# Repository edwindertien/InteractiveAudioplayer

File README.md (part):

# Interactive Audio Player
### Seven wearable players · Teensy 4.1 · 7.1 multichannel audio · NFC hand units · haptics

An embedded system for immersive, location-and-encounter based experiences. Each of up to
seven wearers carries a **hand unit** (NFC reader, distance sensor, vibration motor, LED strip).
Touching a hand unit to an **NFC tag** — another person's tag, a narrator tag, an overlay tag
or the start tag — changes what that wearer hears: the audio, a narration layer, overlays,
sound effects and a haptic channel that is felt through the body. The audio itself is a single
8-channel WAV file on an SD card inside each player.

This README is in two parts.

* **Part I — Operation manual:** preparing audio, the SD card and the configuration files,
  pairing the units, and running a show. Everything here needs no programming.
* **Part II — Building and programming:** hardware, setting up VS Code and PlatformIO, flashing
  the three devices, the project structure, and how the software works.

Background on design decisions, dead ends and open issues lives in [Context.md](Context.md).

> **Figures.** Every figure is a PNG; click it for the zoomable SVG. They are generated by
> `tools/make_docs.py` (see [section 17](#17-regenerating-the-figures)).

## Contents

**Part I — Operation manual**
1. [The system at a glance](#1-the-system-at-a-glance)
2. [The workflow in one picture](#2-the-workflow-in-one-picture)
3. [Preparing the audio](#3-preparing-the-audio)
4. [Preparing the SD card](#4-preparing-the-sd-card)
5. [Tags and the configuration files](#5-tags-and-the-configuration-files)
6. [Pairing hand units and body bridges](#6-pairing-hand-units-and-body-bridges)
7. [Running a show](#7-running-a-show)
8. [Changing files without removing the card (USB mode)](#8-changing-files-without-removing-the-card-usb-mode)
9. [Command reference](#9-command-reference)
10. [Troubleshooting](#10-troubleshooting)

**Part II — Building and programming**

11. [Hardware](#11-hardware)
12. [Setting up the development environment](#12-setting-up-the-development-environment)
13. [Building and flashing](#13-building-and-flashing)
14. [Project structure](#14-project-structure)
15. [How it works](#15-how-it-works)
16. [Tools reference](#16-tools-reference)
17. [Regenerating the figures](#17-regenerating-the-figures)

---

# Part I — Operation manual

## 1. The system at a glance

Each player is a set of three devices plus the wearer's tags:

| Device | What it is | What it does |
|---|---|---|
| **Hand unit** | ESP32-S3 SuperMini + PN532 NFC + VL53L0X distance sensor + vibration motor + 5-LED strip + LiPo | Reads tags, feels the distance to a hand, gives instant feedback (vibration, light) and reports to the body bridge |
| **Body bridge** | ESP32-S3 SuperMini | Receives the hand unit's wireless data (ESP-NOW) and passes it to the Teensy over a two-wire serial link; sends a heartbeat back |
| **Player** | Teensy 4.1 + SD card + PCM5102A (headphones) + MAX98357A (haptics) + LED ring | Plays the experience, decides what a tag means, drives headphones and the haptic transducer |

*Seven players run side by side, each with its own hand unit, body bridge, Teensy and SD card.
The pairs are independent: a hand unit talks to exactly one body bridge.*

## 2. The workflow in one picture

Everything the experience designer edits is a **file**. Nothing in this manual needs a firmware
change. The short version:

1. Export five stems from Ableton and run `assemble_71.sh` → `experience.wav`.  → [section 3](#3-preparing-the-audio)
2. Format the SD cards and copy the files; clean the hidden macOS files.  → [section 4](#4-preparing-the-sd-card)
3. Read the tag UIDs, fill in `tag_catalogue.json`, run `generate_player_configs.py` → seven `config.json`.  → [section 5](#5-tags-and-the-configuration-files)
4. Pair each hand unit with its body bridge.  → [section 6](#6-pairing-hand-units-and-body-bridges)
5. Power everything up and run the show.  → [section 7](#7-running-a-show)

**Tools you need on the Mac/PC:** Python 3, `ffmpeg` (`brew install ffmpeg`), and a serial
monitor (VS Code with PlatformIO, see [section 12](#12-setting-up-the-development-environment),
or any terminal program at 115200 baud).

---

## 3. Preparing the audio

### 3.1 Export the stems from Ableton

Export five files — all **the same length**, on the same tempo grid, **44100 Hz, 16-bit**:

| File | Channels | Content |
|---|---|---|
| `base.wav` | stereo | The main music bed |
| `narr.wav` | **mono** | Narration / operator cues |
| `ov1.wav` | stereo | Overlay stem 1 |
| `ov2.wav` | stereo | Overlay stem 2 |
| `haptic.wav` | **mono** | Low-frequency content that is felt, not heard (the LFE channel) |

*The Ableton arrangement: base, narration, two overlays and the haptic stem exported separately.*

> **Mono export in Ableton:** *File → Export Audio/Video* → tick **Convert to Mono**.

### 3.2 Assemble the 8-channel file

```bash
chmod +x experience/assemble_71.sh
./experience/assemble_71.sh base.wav narr.wav ov1.wav ov2.wav haptic.wav experience.wav
```

The script checks every stem's channel count before merging, so a wrong export can no longer
silently shift every later channel:

* `narr.wav` / `haptic.wav` exported as **stereo** → reduced to mono (`(L+R)/2`; set
  `MONO_MODE=left` to take the left channel only). A dual-mono file keeps its exact level.
* `base.wav` / `ov1.wav` / `ov2.wav` exported as **mono** → duplicated to both channels.
* Anything with more than 2 channels, or a file that is not audio → refused with a message.
* The finished file must be **8 channels at 44100 Hz**; if not, it is deleted and the script
  fails. An existing `experience.wav` is left alone if the script fails before writing.
* **Different stem lengths:** the output is cut to the *shortest* stem. The script prints a
  warning with the shortest and longest length — fix the export, otherwise the end of the
  longer stems is silently lost.

Channel order of `experience.wav` (standard 7.1):

| Index | Name | Content | Goes to |
|---|---|---|---|
| 0 | FL | base L | headphones L (always on) |
| 1 | FR | base R | headphones R (always on) |
| 2 | FC | narration | both ears, fades in/out when toggled |
| 3 | LFE | haptic | MAX98357A → haptic transducer, and the player's LED ring |
| 4 | BL | overlay 1 L | headphones L, fades in/out when toggled |
| 5 | BR | overlay 1 R | headphones R, fades in/out when toggled |
| 6 | SL | overlay 2 L | headphones L, fades in/out when toggled |
| 7 | SR | overlay 2 R | headphones R, fades in/out when toggled |

A 7.5-minute experience is about **317 MB** (450 s × 44 100 × 2 bytes × 8 channels).

### 3.3 The sound effects

Three short effects give feedback for tag events. They are loaded into RAM at boot and played
without touching the SD card.

| File | Played when | Slot |
|---|---|---|
| `fx_connect.wav` | a person tag was accepted (a new chapter starts) | 4 |
| `fx_denied.wav` | a person tag was refused (lock on and not in base, or the show is ending) | 5 |
| `fx_ready.wav` | an encounter has ended and you are back in base, ready for the next | 6 |

**Format requirement: 16-bit PCM, mono, 44.1 kHz, up to about 2 seconds.** The player labels
every effect as mono 44.1 kHz and does not resample, so a stereo or 48 kHz file plays at the
wrong speed. The boot log prints one line per effect, e.g.
`slot 4: fx_connect.wav loaded (1ch 420ms … bytes RAM)` — `1ch` confirms a mono file.

Four older slots (`fx_dev.wav`, `fx_loc_a.wav`, `fx_loc_b.wav`, `fx_boot.wav`, slots 0–3) are
still loaded if present and can be triggered by `"do": "fx"` actions or `on_enter_fx`. If the
files are absent you will see four harmless `cannot open` lines at boot.

While any effect plays, the general audio is **ducked** (lowered) so the effect can be heard —
see `duck_level` in [section 5.4](#54-the-configuration-file-reference).

---

## 4. Preparing the SD card

Use a **SanDisk Ultra or Extreme (A1/A2, UHS-I)** card. A generic Class-4 card produced
audible glitches in testing. 16–32 GB is plenty. The Teensy's **built-in slot** (underside of
the board) is used, not a shield's slot.

### 4.1 What goes on the card

```
/ (SD card root)
├── experience.wav          the 8-channel audio (same file on every card)
├── config.json             this player's configuration (differs per card)
├── fx_connect.wav          effect: a person tag was accepted
├── fx_denied.wav           effect: a person tag was refused
├── fx_ready.wav            effect: back in base, ready for the next encounter
└── led_animations.json     optional: custom LED ring animations
```

`config.json` may also be called `playerN_config.json` (for example `player3_config.json`) so
the card is easy to recognise. The player opens **`/config.json`** if it exists; otherwise it
uses the **one** file in the card root whose name ends in `_config.json`. If there are several
such files it refuses to guess and loads nothing — keep exactly one. Hidden macOS `._…` files and
folders are ignored.

### 4.2 Formatting (macOS)

1. Insert the card, open **Disk Utility**, choose *View → Show All Devices*.
2. Select the **card itself** (the top-level device, not the volume below it).
3. Click **Erase** and set:
   * **Name:** something recognisable, e.g. `PLAYER3`
   * **Format:** **MS-DOS (FAT)** (this is FAT32)
   * **Scheme:** **Master Boot Record**
4. Erase. On Windows use the SD Association's *SD Memory Card Formatter* (FAT32).

### 4.3 Copying the files and cleaning up (macOS)

macOS silently writes hidden files to every FAT volume — `._filename` resource-fork files next to
each file you copy, plus `.DS_Store`, `.Spotlight-V100`, `.fseventsd` and `.Trashes`. They clutter
the directory the Teensy reads, so **always clean the card after copying**:

```bash
cp experience.wav            /Volumes/PLAYER3/
cp output/player3/config.json /Volumes/PLAYER3/
cp fx_connect.wav fx_denied.wav fx_ready.wav /Volumes/PLAYER3/

dot_clean /Volumes/PLAYER3/                      # merge/remove the ._ files
rm -rf /Volumes/PLAYER3/.Spotlight-V100 /Volumes/PLAYER3/.fseventsd /Volumes/PLAYER3/.Trashes
ls -la /Volumes/PLAYER3/                         # should list only your files
diskutil eject /Volumes/PLAYER3
```

Copying from the terminal with `cp` avoids most of the clutter; dragging in Finder creates the most.
**Run `dot_clean` again every time you change something on the card.**

### 4.4 Checking a card

Insert it, power the Teensy and open the serial monitor (115200 baud). A healthy boot shows,
in this order: `[SD] mounted OK`, `[Config] Loaded: 10 chapters, 11 tags (39 uids)…`, one line
per effect, `[Boot] Auto-starting -> 'start_arrival'`, `[Audio] Experience started`. The
complete startup order is in [section 15.5](#155-startup-sequences).

If the **onboard LED on the Teensy blinks fast forever**, the SD card could not be mounted
(wrong format, damaged card, or not inserted).

---

## 5. Tags and the configuration files

### 5.1 Tag roles

| Role | Tag type | What touching it does | Spares | Cooldown |
|---|---|---|---|---|
| **start** | `start` | jump to `base` **and start the show clock** (restarts the show if seen again) | 3 | 2 s |
| **person 1…7** | `person` | start a chapter: your **own** person's tag → `recharge`; the other six → `enc_play`, `enc_suspense`, `enc_loneliness`, `enc_nurture`, `enc_pressure`, `enc_shift` (ascending player number, skipping your own) | 3 per person | 4 s |
| **narrator** | `location` | toggle the narration layer | 3 | 1 s |
| **overlay 1** | `location` | toggle overlay 1 | 6 | 1 s |
| **overlay 2** | `location` | toggle overlay 2 | 6 | 1 s |

*Spares* are additional physical tags for the same role: any of them does the same thing and
they share one cooldown. You can program spares without touching any firmware.

> Overlays reset at every chapter change, because the generated chapters use
> `"overlay_mode": "fresh"`. Change a chapter to `"keep"` if an overlay should survive the change.

### 5.2 Reading a tag's UID

1. Open the Teensy's serial monitor at **115200 baud**.
2. Touch the tag to a paired hand unit.
3. Every detection is logged: `[Bridge] NFC: DE0CC698`. Copy the UID.
4. A tag that is not in the config additionally prints
   `[Bridge] Unknown tag: DE0CC698 -- add to config.json` when it is *confirmed*.

To check which role a UID already has: type `tag DE0CC698` in the Teensy serial monitor.

### 5.3 Generating the seven configs

All seven players share the same chapter timeline; only the `tags` section differs. Both the
timeline and the tag logic are generated by a script from one catalogue file.

1. Fill in **`configs/tag_catalogue.json`** — every physical tag, by role. Empty strings are spare
   slots that are not programmed yet (up to 8 tags per role):

   ```json
   {
     "players":  { "1": ["5040DABE", "", ""], "2": ["1033D9BE", "", ""], "...": [] },
     "start":    ["302FD9BE", "", ""],
     "narrator": ["805ADABE", "", ""],
     "overlay1": ["7034DABE", "", "", "", "", ""],
     "overlay2": ["", "", "", "", "", ""]
   }
   ```

2. Run the generator:

   ```bash
   python3 configs/generate_player_configs.py                 # testing build
   python3 configs/generate_player_configs.py --lock          # show build
   python3 configs/generate_player_configs.py --end-after 12 --duck 0.3
   ```

   | Option | Meaning | Default |
   |---|---|---|
   | `--lock` | person tags are only accepted while `base` is playing | off (switch at any time — for testing) |
   | `--end-after MIN` | minutes after the start tag until the ending begins; `0` = never | 10 |
   | `--duck LEVEL` | general-audio level while an effect plays, 0–1; `1` = no ducking | 0.4 |
   | `--catalogue`, `--out` | other input / output location | `configs/tag_catalogue.json`, `output/` |

3. The result is `output/player1/config.json` … `output/player7/config.json`. The generator
   prints how many tags each role still needs, refuses duplicate, malformed or over-limit UIDs
   (and writes nothing in that case), and warns about roles that have no tags yet.

4. **Re-run it and re-copy the configs to the cards whenever you change the catalogue.**

### 5.4 The configuration file reference

You normally never edit a generated config by hand, but you can: it is plain JSON, and changing
a card needs no reflash. Top level:

```json
{
  "device_id":      "PLAYER_1",
  "start_chapter":  "start_arrival",
  "led_brightness": 120,
  "idle":           { "led": { "animation": "breathe", "color": "0x000066", "intensity": 0.35, "speed": 0.2 } },

  "encounter_lock": false,
  "base_chapter":   "base",
  "sounds":         { "connect": 4, "denied": 5, "ready": 6 },
  "end_after_min":  10,
  "end_chapter":    "end_reflection",
  "duck_level":     0.4,

  "chapters": [ … ],
  "tags":     [ … ]
}
```

| Field | Meaning | If absent |
|---|---|---|
| `device_id` | name shown in the boot log | `UNIT_01` |
| `start_chapter` | chapter that plays from power-on (the waiting room) | `intro` |
| `led_brightness` | global LED brightness, 0–255 | 160 |
| `idle.led` | ring pattern when nothing is playing | — |
| `encounter_lock` | `true`: person tags only accepted in `base_chapter` | `false` |
| `base_chapter` | the hub chapter the lock refers to | `base` |
| `sounds` | RAM effect slot per event; `-1` = silent | all `-1` |
| `end_after_min` | minutes after the start tag until the ending begins (e.g. `0.5`); `0` = never | `0` |
| `end_chapter` | chapter that plays last; when it ends, sound and LEDs go off | `end_reflection` |
| `duck_level` | general audio is lowered to this fraction while an effect plays; `1` = off | `1` (off) |

#### Chapters

```json
{
  "id": "enc_play", "label": "Encounter — Play",
  "start_ms": 135000, "loop_end_ms": 180000,
  "loop": false, "returns_to": "base",
  "on_enter_fx": -1, "overlay_mode": "fresh",
  "overlays": { "ov1": false, "ov2": false, "narr": false },
  "led_background": { "animation": "level", "color": "0xCC4400", "intensity": 0.6, "speed": 0.3 },
  "led_enter":      { "animation": "flash", "color": "0xFFFFFF", "intensity": 0.6, "speed": 0.6, "duration_ms": 600 }
}
```

| Field | Description |
|---|---|
| `id` | unique name, used by tags, `start_chapter`, `returns_to`, `end_chapter` |
| `label` | human-readable name (serial debug and the map) |
| `start_ms` / `loop_end_ms` | the region of `experience.wav` this chapter plays |
| `loop` | `true`: loops between the two times · `false`: plays once |
| `returns_to` | for a non-looping chapter: the chapter to continue with when it ends; empty = go idle |
| `on_enter_fx` | RAM effect slot played on entry, `-1` = none |
| `overlay_mode` | `"fresh"`: apply `overlays` on entry · `"keep"`: inherit the current state |
| `overlays` | default state of `ov1`, `ov2`, `narr` (used when `fresh`) |
| `led_background` | the ring's persistent pattern in this chapter |
| `led_enter` | a one-shot flash when the chapter starts |

The generated timeline is ten 45-second chapters (7:30 in all):

| Chapter | Time | Plays | After it ends |
|---|---|---|---|
| `start_arrival` | 0:00 – 0:45 | loops | — (the waiting room) |
| `base` | 0:45 – 1:30 | loops | — (the hub) |
| `recharge` | 1:30 – 2:15 | once | `base` |
| `enc_play` | 2:15 – 3:00 | once | `base` |
| `enc_suspense` | 3:00 – 3:45 | once | `base` |
| `enc_loneliness` | 3:45 – 4:30 | once | `base` |
| `enc_nurture` | 4:30 – 5:15 | once | `base` |
| `enc_pressure` | 5:15 – 6:00 | once | `base` |
| `enc_shift` | 6:00 – 6:45 | once | `base` |
| `end_reflection` | 6:45 – 7:30 | once | sound and LEDs off |

To change the chapter times or LED colours for all seven cards, edit the `CHAPTERS` list in
`configs/generate_player_configs.py` and regenerate.

#### Tags and actions

```json
{
  "label": "Meet player 2 -> enc_play",
  "type": "person",
  "cooldown_ms": 4000,
  "uids": ["1033D9BE", "1033000A", "1033000B"],
  "actions": [ { "do": "chapter", "target": "enc_play" } ]
}
```

| Field | Description |
|---|---|
| `uid` and/or `uids` | one UID, or a list of spares (up to 8), upper-case hex; lower case is accepted and converted. A UID listed under two roles gives a warning; the first entry wins |
| `label` | description, shown in logs |
| `type` | `person`, `start`, `location` or the legacy `device`. Only `person` is affected by the lock and the ending; only `start` starts the clock |
| `cooldown_ms` | minimum time between two accepted touches of this role |
| `actions` | what to do (below) |

| `"do"` | Parameters | Effect |
|---|---|---|
| `"chapter"` | `"target": "id"` | jump to a chapter with a crossfade |
| `"overlay"` | `"target": "ov1"/"ov2"/"narr"`, `"value": "on"/"off"/"toggle"` | fade a layer in or out |
| `"fx"` | `"slot": 0-7` | play a RAM effect |
| `"led"` | `animation`, `color`, `intensity`, `speed`, `duration_ms` | a one-shot ring event |

A card holds at most **32 tag entries**; because spares share an entry, the full catalogue
(39 physical tags per card) needs only 11.

#### LED animations

Parameters: `color` = `"0xRRGGBB"` · `intensity` = 0–1 · `speed` = 0–1 · `duration_ms` (one-shots only).

| Name | Uses colour | Description |
|---|---|---|
| `level` | ✓ | **haptic sync** — the live envelope of the LFE channel |
| `heartbeat` | ✓ | **haptic sync** — a lub-dub shape |
| `breathe` | ✓ | smooth pulse between 25 % and 100 % |
| `solid` | ✓ | constant colour |
| `sparkle` | tint | dim base with random sparks |
| `fire` · `ocean` · `rainbow` | — | own palettes |
| `pulse_ring` | ✓ | ring expanding from the centre |
| `spin` | ✓ | an arc rotating around the ring |
| `flash` | ✓ | three quick flashes, then a dim hold |
| `confetti` | tint | random colour bursts |
| `comet` | ✓ | a dot racing with a trail |
| `off` | — | dark |

Custom animations are drawn with `tools/led_editor.py` and saved as `led_animations.json`
on the card; use the animation's `id` in any `animation` field. The animator checks custom ids
*before* the built-in names, so give custom animations distinct names.

### 5.5 Looking at a configuration

`experience/Visualise.py` draws a configuration: chapters on a timeline, overlay defaults, LED
colours, where every chapter goes when it ends, the start and end chapter, and which tag does what.

```bash
python3 experience/Visualise.py output/player1/config.json map.html --svg map.svg --png map.png
```

*Player 1's card. The tag rows show the first UID of each role and `+N` for its spares. Open
`docs/experience_map.html` for the same map in a browser.*

### 5.6 Editing tools and their limits

| Tool | Use it for | Limits |
|---|---|---|
| `configs/generate_player_configs.py` | **the normal way**: tags, timeline, show settings for all seven cards | chapter list is in the script |
| `tools/led_editor.py` | designing custom ring animations (`led_animations.json`) and previewing the built-ins | — |
| `tools/editor.py` | a web editor (http://localhost:8080) for one `config.json`: chapters, LEDs, overlays | shows only a single `uid` box and the old `location`/`device` types; it does **not** edit `uids` lists, `person`/`start` types or the newer top-level settings. It keeps them when it saves (it writes the whole object back), but edit those in a text editor |

Keep the generator's output as the master: if you hand-edit one card, remember that regenerating
overwrites it.

---

## 6. Pairing hand units and body bridges

A hand unit and a body bridge must be **paired** once; each stores the other's MAC address in
flash, so the pairing survives reboots and sleep. Pairing needs both units powered, close together,
and the hand unit **awake** — see the power notes in [section 7.1](#71-switching-on-and-off).

### Method A — from the hand unit's serial CLI (verified)

1. Power the body bridge. Connect the hand unit to the computer, wake it (press its button) and
   open its serial monitor (115200 baud).
2. Type `espnow scan`. The hand unit broadcasts a PING, the body bridge pairs with the sender and
   answers; the hand unit pairs on the answer.
3. Both status LEDs turn **green**. In the hand unit's monitor you see `Paired: <MAC>` and then a
   `rx type=0x12` line every second (the heartbeat).

The body bridge pairs with **whichever hand unit pings**. With several pairs in one room, pair one
set at a time (power the others off) or use method B.

### Method B — with the two buttons

1. On the **body bridge**, hold the button (GPIO 9) for 2 seconds. Its status LED blinks **blue**
   fast: pairing mode, for up to 30 seconds. It broadcasts a pairing request every 300 ms.
2. The hand unit's status LED starts blinking **blue**: a request is pending.
3. **Tap the hand unit's button** (shorter than 2 seconds — a longer press puts it to sleep).
4. Both LEDs turn **green** and pairing mode ends.

Only the body bridge in pairing mode can be paired this way, so it is the safe method for several
pairs in one room. *Status: implemented and part of the firmware; this procedure had not been
confirmed end to end when this manual was written — if it fails, use method A and see
[Context.md](Context.md).*

### Checking and clearing

| | Hand unit | Body bridge |
|---|---|---|
| Show the pairing | `espnow` | `status` |
| Forget the pairing | `espnow clear` | `clear` |
| Set a peer by hand | `espnow bind <MAC>` | — |
| This unit's MAC | printed at boot (`[ESPNOW] MAC: …`) | `mac` |

`espnow bind <MAC>` sets only the **hand unit's** side of the pairing. The body bridge ignores data from a hand unit it has not
paired with (by `espnow scan` or the buttons), so `bind` alone is not a way to pair. *(Read from the code; not tested.)*

*What the status LEDs mean on the hand unit and the body bridge.*

Label each pair (a sticker with the player number on both) — the units are otherwise identical.

---

## 7. Running a show

### 7.1 Switching on and off

* **Hand unit.** Connecting the battery or pressing reset makes the unit go **straight back to
  sleep**; **press the button** to start it. Once it is running, **hold the button for 2 seconds** to
  put it to sleep (the status LED flashes orange to confirm); press it again to wake. At start-up
  the LED strip lights **green** (NFC reader and distance sensor both found) or **amber** (one is
  missing), with two short vibration pulses.
* **Body bridge.** Powered whenever its supply is on; it has no sleep mode.
* **Player (Teensy).** Starts playing the waiting room as soon as it is powered — no tag needed.

The battery is monitored every 10 s: **orange fast pulse** on the status LED below 3.6 V, automatic
sleep below 3.3 V. On USB the battery cannot be measured and the unit says so
(`USB powered … battery not measurable`). See [section 9.2](#92-hand-unit-serial-monitor-115200-baud) for calibration.

### 7.2 A show

1. **Waiting room.** `start_arrival` loops from power-on.
2. **Start tag.** The wearer touches the start tag: `base` starts and the show clock begins.
3. **Encounters.** Touching another person's tag starts that encounter chapter (about 45 s) with the
   *connect* sound. Touching your own tag starts `recharge`. When the chapter ends you are back in
   `base` with the *ready* sound. With `--lock` (show build) a person tag is only accepted in `base`;
   anywhere else it gets the *denied* sound. Without it (testing build) person tags switch at any time.
4. **Layers.** Narrator and overlay tags toggle that layer in every state. Effects play from RAM and the
   general audio ducks while one plays.
5. **The ending.** `end_after_min` after the start tag the show wraps up: the chapter that is playing
   finishes (a looping chapter such as `base` finishes its current pass), new person tags are refused,
   then `end_reflection` plays.
6. **Over.** When `end_reflection` ends, the player's **sound and LED ring go off**. Hand units and body
   bridges keep running. Only the **start tag** is accepted now; it begins a new show from `base`.
   Rebooting the player also restarts everything.

Testing without waiting: `show 0.5` on the Teensy sets the ending to 30 seconds, `show end`
forces it now, `show start` does what the start tag does, `show` prints the state.

### 7.3 Before the doors open — checklist

- [ ] Every card has `experience.wav`, one `config.json`, the three effects; `dot_clean` was run
- [ ] Show build of the configs (`--lock`, the right `--end-after`)
- [ ] Hand units charged; each paired (green status LED) and labelled with its player number
- [ ] The Teensy log shows `[Config] Loaded …`, three effects loaded, no `Unknown tag` for any tag you hand out
- [ ] Each tag works: touch it, see the right chapter/overlay change in the Teensy log
- [ ] Headphones plugged in, volume pot where you want it, haptic transducer felt
- [ ] A last full run with `show 1` to hear the ending and the switch-off

---

## 8. Changing files without removing the card (USB mode)

The SD card sits under the Teensy and is awkward to remove. **USB maintenance mode** shares the card
with the computer over the Teensy's USB cable while the board stays in its case.

1. Connect the Teensy by USB and open the serial monitor (115200 baud).
2. Type **`usb`**. Playback stops, the LED ring spins **cyan**, and the card is shared over **MTP** as
   `SD Card`.
3. Open an **MTP client** on the computer. macOS has no built-in MTP support; use a third-party client
   (OpenMTP is one). Copy `config.json`, `experience.wav` or effects across.
4. Type **`reboot`**. The player restarts and reloads everything.

While in USB mode the player ignores tags and every command except `reboot` — the card belongs to the
computer. Large files (`experience.wav` is ~300 MB) take a while. If you also used Finder on the card,
run `dot_clean` once it is back in a reader.

---

## 9. Command reference

All three devices have a serial console at **115200 baud**. Commands are typed in the
monitor and confirmed with Enter.

### 9.1 Teensy player

| Command | Effect |
|---|---|
| `chapters` | list the chapters: times, loop or once, effect, LED, where they go next |
| `tags` | list the tag entries: first UID, number of UIDs, type, label, actions |
| `tag <uid>` | which role does this UID have? |
| `go <id>` | jump to a chapter (starts the audio if it is not running) |
| `seek <ms>` | seek to a raw time |
| `narr` · `ov1` · `ov2` | toggle that layer |
| `fx <n>` | play RAM effect slot *n* (`fx 4`, `fx 5`, `fx 6` test the three feedback sounds) |
| `bridge` | state of the link to the body bridge: alive, age of the last message, distance, touch |
| `show` | the show state: waiting, running (minutes elapsed), ending, over |
| `show <minutes>` | set the time until the ending (`show 0.5`); `show 0` = never. Not saved |
| `show start` / `show end` | do what the start tag does / force the ending now |
| `lock [on\|off]` | person tags only accepted in `base` / at any time. Not saved |
| `duck [0-1]` | show or set the ducking level (`duck 0.3`; `1` = off). Not saved |
| `haptic` · `haptic reset` | haptic settings and the loudest haptic peak seen · clear that peak |
| `hdrive <k>` | haptic soft-limiter drive, 0 = bypass … 8 (the default is 0.5) |
| `hgain <g>` | haptic mixer gain 0–4 (above 1 the mixer hard-clips — use `hdrive` for loudness) |
| `usb` | enter USB maintenance mode ([section 8](#8-changing-files-without-removing-the-card-usb-mode)) |
| `reboot` | restart the player |

Values set from the console are not saved; put the final value in the configuration (or the
`#define` at the top of `main.cpp`).

### 9.2 Hand unit (serial monitor, 115200 baud)

| Command | Effect |
|---|---|
| `help` | the command list |
| `status` · `debug` | all sensor readings · dump all state |
| `stream` | toggle a live distance stream |
| `scan` | I²C scan |
| `rainbow` · `solid <r> <g> <b>` · `bright <0-255>` · `off` · `idle` | LED test modes |
| `motor <pulses>` | trigger a vibration burst |
| `nfc` | re-run NFC init and poll for 3 s |
| `sleep` | go to deep sleep |
| `espnow` · `espnow scan` · `espnow bind <MAC>` · `espnow clear` · `espnow test` | pairing and link ([section 6](#6-pairing-hand-units-and-body-bridges)) |
| `battery` | battery level, rail voltage, divider-pin voltage, offset |
| `battery cal <batV> <pinV>` | set this unit's offset from two multimeter readings taken **on battery**: the voltage at the battery terminals and at GPIO 3, e.g. `battery cal 3.80 1.74` |
| `battery offset <mV>` · `battery clear` | set the offset directly · back to the default |
| `tof` | distance-sensor diagnostics: settings, counters, status codes seen |
| `tof raw` | toggle: print every measurement with its status, signal rate and SPAD count |
| `tof rate <mcps>` · `tof budget <ms>` · `tof period <ms>` · `tof long on\|off` | sensor tuning |
| `tof min <mm>` · `tof max <mm>` | the window of readings that count |
| `tof defaults` · `tof save` · `tof clear` · `tof reset` | defaults · store/erase this unit's settings in flash · clear counters |

**Battery:** the voltage divider on this board hangs on the board's 5 V rail behind a Schottky diode,
so on battery the reading is the cell voltage minus about 0.3 V. The firmware adds a per-unit offset
(default 320 mV) and treats any rail above 4.3 V as USB power ("battery not measurable").

### 9.3 Body bridge

| Command | Effect |
|---|---|
| `status` | pairing, last packet, counters for the paired hand, uptime, foreign traffic |
| `mac` | this unit's MAC address |
| `stream` | toggle a continuous proximity stream |
| `clear` | forget the paired hand unit |
| `help` · `?` | the list |

---

## 10. Troubleshooting

| Symptom | Likely cause | What to do |
|---|---|---|
| Teensy's onboard LED blinks fast forever | SD card not mounted | reformat FAT32 ([4.2](#42-formatting-macos)); check the card is seated |
| `[Config] ERROR: cannot open /config.json` | no `config.json`, or it is named something else | name it `config.json`, or keep exactly one `*_config.json` ([4.1](#41-what-goes-on-the-card)) |
| `[Config] ERROR: … files match *_config.json` | several `*_config.json` on the card | remove all but one |
| No headphone sound, haptics fine | PCM5102A muted: its `H3L` (XSMT) jumper is not bridged to **HIGH** | bridge `H3L` to H; `H1L`, `H2L`, `H4L` to L |
| No haptics, headphones fine | MAX98357A in shutdown: its SD pin must be tied to VIN | check the wiring ([11.3](#113-the-audio-boards)) |
| No audio and `[Audio] ERROR: experience.wav not found` | file missing or misnamed | check the card; run `dot_clean` |
| Stuttering / clicking audio | slow card, or hidden macOS files | SanDisk A1/A2 card; `dot_clean` |
| Hand unit "does nothing" after connecting power | it goes to sleep after a reset | press the button once |
| Start-up LEDs are **amber**, or `nfc` finds no reader | the PN532 is not in UART mode, is miswired, or its reset line is wrong | DIP switches SEL0 = SEL1 = LOW; wiring GPIO 5 / 6 / 10 ([11.2](#112-pinouts)); the init sequence is in [Context.md](Context.md) |
| Status LED **red** | not paired | pair ([6](#6-pairing-hand-units-and-body-bridges)) |
| Status LED **yellow** | paired, but the other unit is not answering | is the other unit on? in range? same pair? |
| LED colours swapped (red shows green) | a **v0.0.2** SuperMini board (RGB order); the standard board is GRB | use the standard board, or build with `-DSTATUS_LED_ORDER=RGB` |
| Touching a tag does nothing | the UID is not in the config (`Unknown tag` in the log); or the tag's cooldown has not elapsed; or the show is over / ending / locked | check the log: it says why (`ignored`, `refused`, `cooling down`) |
| After the show nothing responds | the show is over | touch the **start tag**, or reboot the player |
| A person tag gets the *denied* sound | the lock is on and you are not in `base`, or the show is ending | finish the chapter first; `lock off` for testing |
| Effects are inaudible | the general audio is too loud | set `duck_level` lower ([5.4](#54-the-configuration-file-reference)); try `duck 0.3` live |
| An effect plays too slowly / too long | file is stereo or not 44.1 kHz | re-export mono 16-bit 44.1 kHz |
| `assemble_71.sh` reports a channel count problem | a stem has the wrong number of channels | re-export; the message names the file |
| Output shorter than the stems | stems have different lengths; the output is cut to the shortest | re-export all stems with the same length |
| Hand-unit battery shows 4.8 V | the unit is on USB: the rail is USB power | run on battery; calibrate with `battery cal` |
| Orange low-battery pulse at a real 3.8 V | missing diode correction | `battery cal <batV> <pinV>` |
| Distance sensor only reacts when very close | weak return signal, or the signal-rate limit | run `tof raw` and read the status codes and signal rate; compare with a good unit ([Context.md](Context.md)) |
| Build error `'FS' has not been declared` / `redefinition of 'class MTPStorage'` (Teensy) | FastLED 3.10.2/3.10.3 with the MTP USB type, or the external MTP library added | keep FastLED at 3.10.1; do not add the MTP_Teensy library ([12.3](#123-library-and-platform-pins)) |
| ESP32 build error about ESP-NOW callback signatures | wrong Arduino core (3.x) | pin `platformio/espressif32@6.13.0` ([12.3](#123-library-and-platform-pins)) |

---

# Part II — Building and programming

## 11. Hardware

### 11.1 Parts

| Part | Notes |
|---|---|
| Teensy 4.1 | 600 MHz Cortex-M7; built-in SDIO SD slot; USB serial + MTP |
| PCM5102A DAC module | headphone audio on I²S 1; solder-jumper settings below |
| MAX98357A amplifier module | haptic transducer on I²S 2 |
| Headphones with built-in amplifier | an analog potentiometer reduces the level |
| 16-LED ring (SK6812 / WS2812) | on the player, pin 14 |
| 2 × ESP32-S3 SuperMini | one for the hand unit, one for the body bridge. Use the **standard** boards, not v0.0.2 (different LED colour order and USB wiring) |
| PN532 NFC module | hand unit; DIP switches **SEL0 = LOW, SEL1 = LOW** (UART / HSU mode) |
| VL53L0X time-of-flight module | hand unit; distance to a hand |
| Vibration motor | hand unit; switched by an N-channel MOSFET from a PWM pin |
| 5-LED WS2812B strip | hand unit; an 8-LED strip cut down to 5 (the player has its own 16-LED ring) |
| LiPo battery (1S, 3.0–4.2 V) | hand unit; charged through the SuperMini's TP4054 |
| Push buttons | hand unit (GPIO 9), body bridge (GPIO 9) |
| SanDisk Ultra / Extreme A1 or A2 SD card | one per player |

### 11.2 Pinouts

**Teensy 4.1**

| Function | Pins |
|---|---|
| I²S 1 → PCM5102A | MCLK 23 · BCLK 21 · LRCLK 20 · DIN 7 |
| I²S 2 → MAX98357A | LRC 3 · BCLK 4 · DIN 2 |
| Body-bridge UART (Serial1, 115200) | pin 0 (RX1) ← bridge GPIO 43 (TX) · pin 1 (TX1) → bridge GPIO 44 (RX) · common GND |
| LED ring (16 × SK6812) | pin 14, 5 V and GND (an external 5 V supply is recommended) |
| SD card | built-in SDIO slot |
| Onboard LED | pin 13: fast blink = SD mount failed |

**Hand unit — ESP32-S3 SuperMini**

| Function | GPIO |
|---|---|
| LED strip (WS2812B, 5 LEDs, GRB) | 4 |
| Vibration motor (PWM 20 kHz, 8 bit) | 2 |
| VL53L0X: SDA / SCL / XSHUT | 7 / 8 / 1 |
| PN532 (UART 115200): TX / RX / RST | 6 / 5 / 10 |
| Status LED (onboard RGB) | 48 |
| Button (to GND, internal pull-up) | 9 |
| Battery divider (1:2, equal resistors) | 3 |

**Battery divider.** Two equal resistors (100 kΩ each according to `Config.h`; a comment in `PowerManager.h` says 220 kΩ — measure
your board), mid-point to GPIO 3. The original design notes show a 100 nF capacitor from GPIO 3 to ground. The top of the divider is on
the SuperMini's **5 V rail**, not directly on the cell — see [Context.md](Context.md) and [section 9.2](#92-hand-unit-serial-monitor-115200-baud).

**Hand-unit LED strip.** The hand unit's ring was replaced by a strip of **5 WS2812B LEDs**, an 8-LED strip cut down to size. Cut it at the
strip's marked cut line (between two LEDs) and keep the end with the data-in arrow towards the ESP32 — as with any WS2812 strip, only the
first LED's data-in is wired (to GPIO 4, with 5 V and GND). Then set `LED_COUNT` in `ESP32handUnit/src/Config.h` to **5** and reflash.
The firmware depends on the count only through `LED_COUNT` (the array, the driver setup, and the spacing of the idle wave and of the
`rainbow` test, which is `256 / LED_COUNT`). The 16-LED ring described for the **player** (Teensy pin 14) is a different part and is unchanged.

**Body bridge — ESP32-S3 SuperMini**

| Function | GPIO |
|---|---|
| Teensy UART (Serial1, 115200): TX / RX | 43 / 44 |
| Status LED (onboard RGB) | 48 |
| Pair button (to GND, internal pull-up) | 9 |

### 11.3 The audio boards

* **PCM5102A:** its four solder jumpers set the filter, de-emphasis, soft-mute and format. Bridge
  `H1L` (FLT) to L, `H2L` (DEMP) to L, **`H3L` (XSMT) to H**, `H4L` (FMT, I²S) to L. The factory
  default leaves `H3L` low, which keeps the output muted. The module's `SCK` pin is grounded
  (its internal PLL generates the clock).
* **MAX98357A:** tie **SD to VIN** (it has an internal pull-down, so a floating SD pin means
  shutdown). GAIN floating gives 9 dB; GAIN to GND 12 dB; GAIN through 100 kΩ to GND 15 dB (per the
  datasheet).
* The haptic signal is mono and is sent to both I²S 2 channels.

### 11.4 PCBs

Two boards were designed for this project. Schematics and board layouts are exported as PNG (shown
here) and PDF. *The files in `docs/` are placeholders until the real exports are dropped in under the
same names.*

**Player PCB** — Teensy 4.1 carrier with the PCM5102A, the MAX98357A, the LED-ring connector and the
bridge UART.

| Schematic | Board layout |
|---|---|
|  |  |
| [PDF](docs/pcb_player_schematic.pdf) | [PDF](docs/pcb_player_board.pdf) |

**Hand unit PCB** — ESP32-S3 SuperMini, PN532, VL53L0X, motor driver, LED strip and battery.

| Schematic | Board layout |
|---|---|
|  |  |
| [PDF](docs/pcb_hand_unit_schematic.pdf) | [PDF](docs/pcb_hand_unit_board.pdf) |

---

## 12. Setting up the development environment

### 12.1 Install

1. **VS Code** — <https://code.visualstudio.com>.
2. In VS Code, install the **PlatformIO IDE** extension (it installs its own Python and the `pio`
   command). Restart VS Code when asked.
3. **Python 3** and **ffmpeg** for the tools: `brew install python ffmpeg` on macOS. The Python tools were
   tested with Python 3.9 (the version macOS ships), 3.11 and 3.12; check yours with `python3 --version`.
4. For the documentation figures only: `pip install cairosvg pillow`.
5. Clone the repository and open each device's folder in VS Code (below).

The repository holds **three PlatformIO projects**; open each as its own workspace (or add them
as a multi-root workspace):

| Folder | Device | Environment |
|---|---|---|
| repository root (`platformio.ini`) | Teensy player | `teensy41` |
| `ESP32handUnit/` | hand unit | `hand_unit` |
| `ESP32bodyBridge/` | body bridge | `body_bridge` |

PlatformIO downloads the platforms and libraries on the first build.

### 12.2 Serial ports

On macOS the boards appear as `/dev/cu.usbmodem…`. List them with `pio device list`. With several
boards connected, select the port explicitly (`--port` for the monitor, `--upload-port` for uploads).
The Teensy's port changes when its USB type changes (it is *Serial + MTP* here).

### 12.3 Library and platform pins

These versions were tested together. **Do not float them** — the toolchain moved underneath this
project several times (details in [Context.md](Context.md)).

| Project | Pin | Why |
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
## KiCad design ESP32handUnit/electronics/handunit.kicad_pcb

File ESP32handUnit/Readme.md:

# Hand Unit — ESP32-S3 Super Mini

Wearable hand unit for the KEIKEN immersive performance project. Detects proximity and NFC tag contact, drives haptic feedback and LED animation, and communicates wirelessly with a body bridge unit via ESP-NOW.

---

## Hardware

| Component | Part |
|---|---|
| MCU | ESP32-S3 Super Mini (ESP32-S3FH4R2, 4MB flash, 2MB PSRAM) |
| NFC reader | PN532 module — UART/HSU mode |
| Proximity sensor | VL53L0X ToF (I2C) |
| LED ring | 8× WS2812B NeoPixel |
| Status LED | Onboard WS2812B (GPIO48) |
| Vibration motor | Via N-channel MOSFET, PWM |
| Power button | Momentary, to GND |
| Battery | 1S LiPo, voltage divider to ADC |

---

## Pin Assignments

| Signal | GPIO | Notes |
|---|---|---|
| NeoPixel ring | 4 | WS2812B data |
| Motor PWM | 2 | LEDC channel 0, 20kHz |
| VL53L0X SDA | 7 | Wire (I2C0) |
| VL53L0X SCL | 8 | Wire (I2C0) |
| VL53L0X XSHUT | 1 | Active LOW shutdown |
| PN532 TX (ESP→PN532 RX) | 6 | UART1 |
| PN532 RX (ESP←PN532 TX) | 5 | UART1 |
| PN532 RST | 10 | Active LOW reset |
| Status LED | 48 | Onboard WS2812B |
| Power button | 9 | To GND, internal pull-up |
| Battery ADC | 3 | 100kΩ+100kΩ divider (1:2) |

### PN532 DIP Switches (UART mode)
```
SEL0 = LOW  (0)
SEL1 = LOW  (0)
```

### Battery Voltage Divider
```
VBAT ──── 100kΩ ──┬── 100kΩ ──── GND
                  │
               GPIO3 (+ 100nF cap to GND)
```

---

## Power On / Off

**Turn on:** press button once (wakes from deep sleep)  
**Turn off:** hold button for 2 seconds (long press)  
**Default state:** device boots into deep sleep — button is required to start

On fresh battery connection the device immediately enters deep sleep. The PN532 is held in reset (GPIO10 LOW, latched) during sleep. The VL53L0X is in hardware standby (XSHUT LOW, latched). Current in sleep: ~20µA (ESP32) + ~5µA (PN532) + ~5µA (VL53L0X).

---

## LED Ring Behaviour (8× NeoPixel, GPIO4)

| State | Colour | Pattern |
|---|---|---|
| Idle, nothing nearby | Teal | Travelling sine wave, ~3.8s rotation |
| Object approaching | Teal → red | Colour shifts with proximity |
| NFC tag contact | White | 80ms flash |
| Post-connection silence | Teal | No colour shift (motor suppressed) |

## Status LED Behaviour (GPIO48)

| Colour | Pattern | Meaning |
|---|---|---|
| 🔴 Red | Slow breathe | Not paired with body bridge |
| 🟡 Amber | Pulse | Paired, no recent heartbeat |
| 🟢 Green | Gentle breathe | Active ESP-NOW link |
| ⚪ White | 400ms flash | NFC tag detected |
| 🔵 Cyan | 800ms flash | Touch/connection event |

---

## Interaction Sequence

1. **Proximity detected** (VL53L0X < 300mm): vibration motor ramps up quadratically; LED shifts teal→red
2. **NFC tag contact**: motor fires double-click (2 pulses, 40ms on/30ms off); LED flashes white
3. **Silence period** (3 seconds): motor off regardless of proximity; LED stays teal; new connections blocked
4. **Separation** (object leaves field AND silence expired): returns to idle

---

## ESP-NOW Pairing

1. Note body bridge MAC from its serial output: `Body bridge MAC: XX:XX:XX:XX:XX:XX`
2. On hand unit serial: `espnow scan` — broadcasts PING, waits for PONG
3. Or manually: `espnow bind XX:XX:XX:XX:XX:XX`
4. Pairing stored in NVS — survives power cycles

---

## CLI Commands (serial monitor, 115200 baud)

| Command | Action |
|---|---|
| `status` | All sensor and system state |
| `debug` | Verbose pin/state dump |
| `stream` | Toggle VL53L0X distance stream |
| `scan` | I2C bus scan |
| `nfc` | Re-run NFC init + 3s tag poll |
| `rainbow` | LED rainbow animation |
| `solid <r> <g> <b>` | Solid LED colour |
| `bright <0-255>` | LED brightness |
| `off` / `idle` | LED off / return to proximity mode |
| `motor <n>` | Fire n-pulse motor burst |
| `sleep` | Immediate deep sleep |
| `battery` | Read battery voltage |
| `espnow` | ESP-NOW status |
| `espnow scan` | Discover body bridge |
| `espnow bind <MAC>` | Manual peer set |
| `espnow clear` | Clear stored pairing |
| `espnow test` | Send test packet |

---

## Config.h Parameters

| Define | Default | Description |
|---|---|---|
| `POWER_MANAGEMENT` | `1` | `0` = always on (debug), `1` = full sleep/wake |
| `NFC_SLEEP_MS` | `0` | PN532 PowerDown between polls (0=always on, 200=~8mA avg) |
| `SILENCE_MS` | `3000` | Post-connection motor silence in ms |
| `PROX_FAR_MM` | `300` | Proximity detection range |
| `PROX_NEAR_MM` | `40` | Near threshold (motor at max) |
| `MOTOR_FREQ` | `20000` | PWM frequency (20kHz = inaudible) |
| `MOTOR_MAX` | `200` | Maximum motor duty (0–255) |
| `POWER_HOLD_MS` | `2000` | Long-press duration to sleep |
| `VBAT_LOW_MV` | `3600` | Battery low warning threshold |
| `VBAT_CRIT_MV` | `3300` | Battery critical → auto shutdown |
| `USE_LONG_PRESS` | `1` | `1`=long press, `0`=double tap to sleep |

---

## File Structure

```
hand-unit/
  platformio.ini
  README.md
  context.md
  src/
    Config.h          — all pin assignments and parameters
    Motor.h           — esp_timer burst, proximity motor
    Proximity.h       — VL53L0X non-blocking reads
    TouchManager.h    — connection state machine (IDLE/RELEASED)
    LedRing.h         — NeoPixel animations
    NfcTask.h         — PN532 UART, FreeRTOS Core 0 task, queue
    EspNow.h          — ESP-NOW pairing, send functions
    StatusLed.h       — GPIO48 status indicator
    PowerManager.h    — deep sleep, button, battery
    Cli.h             — serial command handler
    main.cpp          — setup() + loop()
```

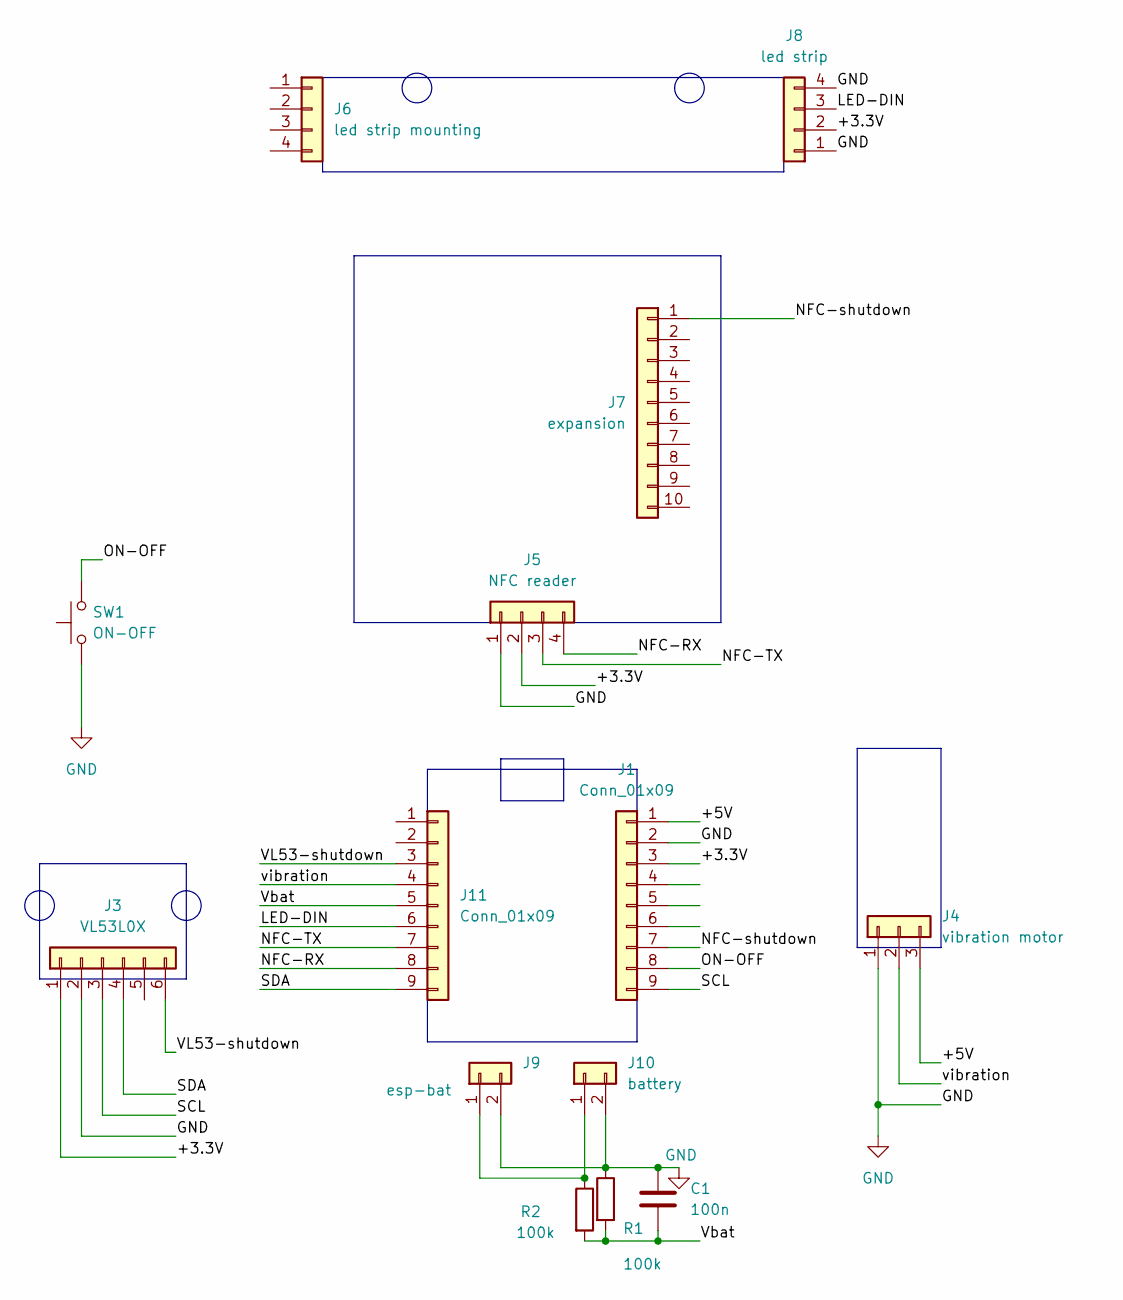
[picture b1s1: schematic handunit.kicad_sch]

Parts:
C1: 100n; C_0603_1608Metric_Pad1.08x0.95mm_HandSolder
J1, J11: Conn_01x09; PinHeader_1x09_P2.54mm_Vertical
J3: VL53L0X; PinHeader_1x06_P2.54mm_Vertical
J4: vibration motor; PinHeader_1x03_P2.54mm_Vertical
J5: NFC reader; PinHeader_1x04_P2.54mm_Vertical
J6: led strip mounting; PinHeader_1x04_P2.54mm_Horizontal
J7: expansion; PinHeader_1x10_P1.27mm_Vertical
J8: led strip; PinHeader_1x04_P2.54mm_Horizontal
J9: esp-bat; JST_EH_B2B-EH-A_1x02_P2.50mm_Vertical
J10: battery; JST_EH_B2B-EH-A_1x02_P2.50mm_Vertical
R1, R2: 100k; R_0603_1608Metric_Pad0.98x0.95mm_HandSolder
SW1: ON-OFF; SW_PUSH_6mm

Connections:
/+3.3V: J1.3, J3.1, J5.2, J8.2
/+5V: J1.1, J4.3
/LED-DIN: J8.3, J11.6
/NFC-RX: J5.4, J11.8
/NFC-TX: J5.3, J11.7
/NFC-shutdown: J1.7, J7.1 (Pin_1_1)
/ON-OFF: J1.8, SW1.2
/SCL: J1.9, J3.3
/SDA: J3.4, J11.9
/VL53-shutdown: J3.6, J11.3
/Vbat: C1.2, J11.5, R1.2, R2.2
/vibration: J4.2, J11.4
GND: C1.1, J1.2, J3.2, J4.1, J5.1, J8.1, J8.4, J9.2, J10.2, R1.1, SW1.1
unnamed: J9.1, J10.1, R2.1

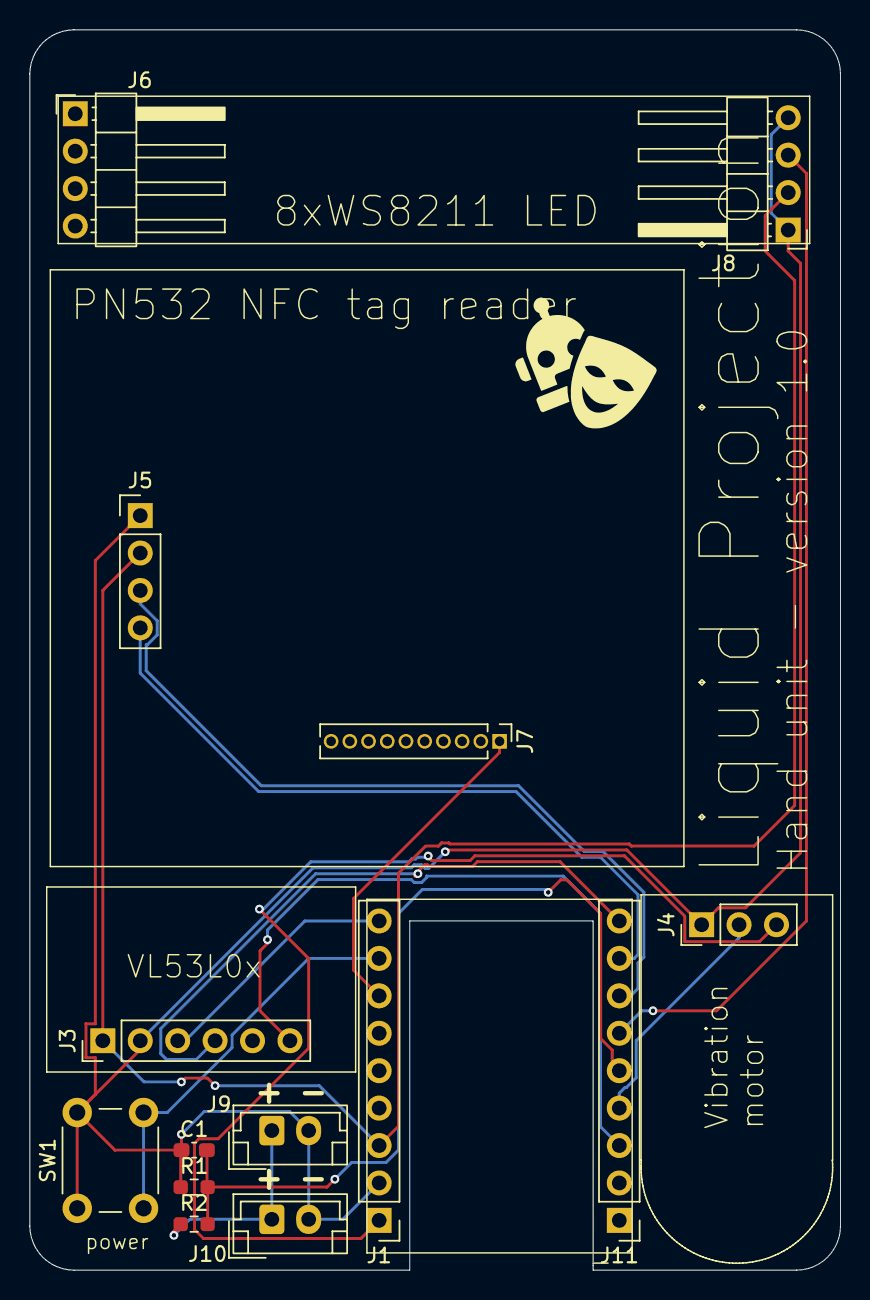
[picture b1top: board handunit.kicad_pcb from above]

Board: 2 copper layers, 55.0 x 84.2 mm, 15 parts (0 on the bottom side), 14 nets.

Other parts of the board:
G: LOGO; logo

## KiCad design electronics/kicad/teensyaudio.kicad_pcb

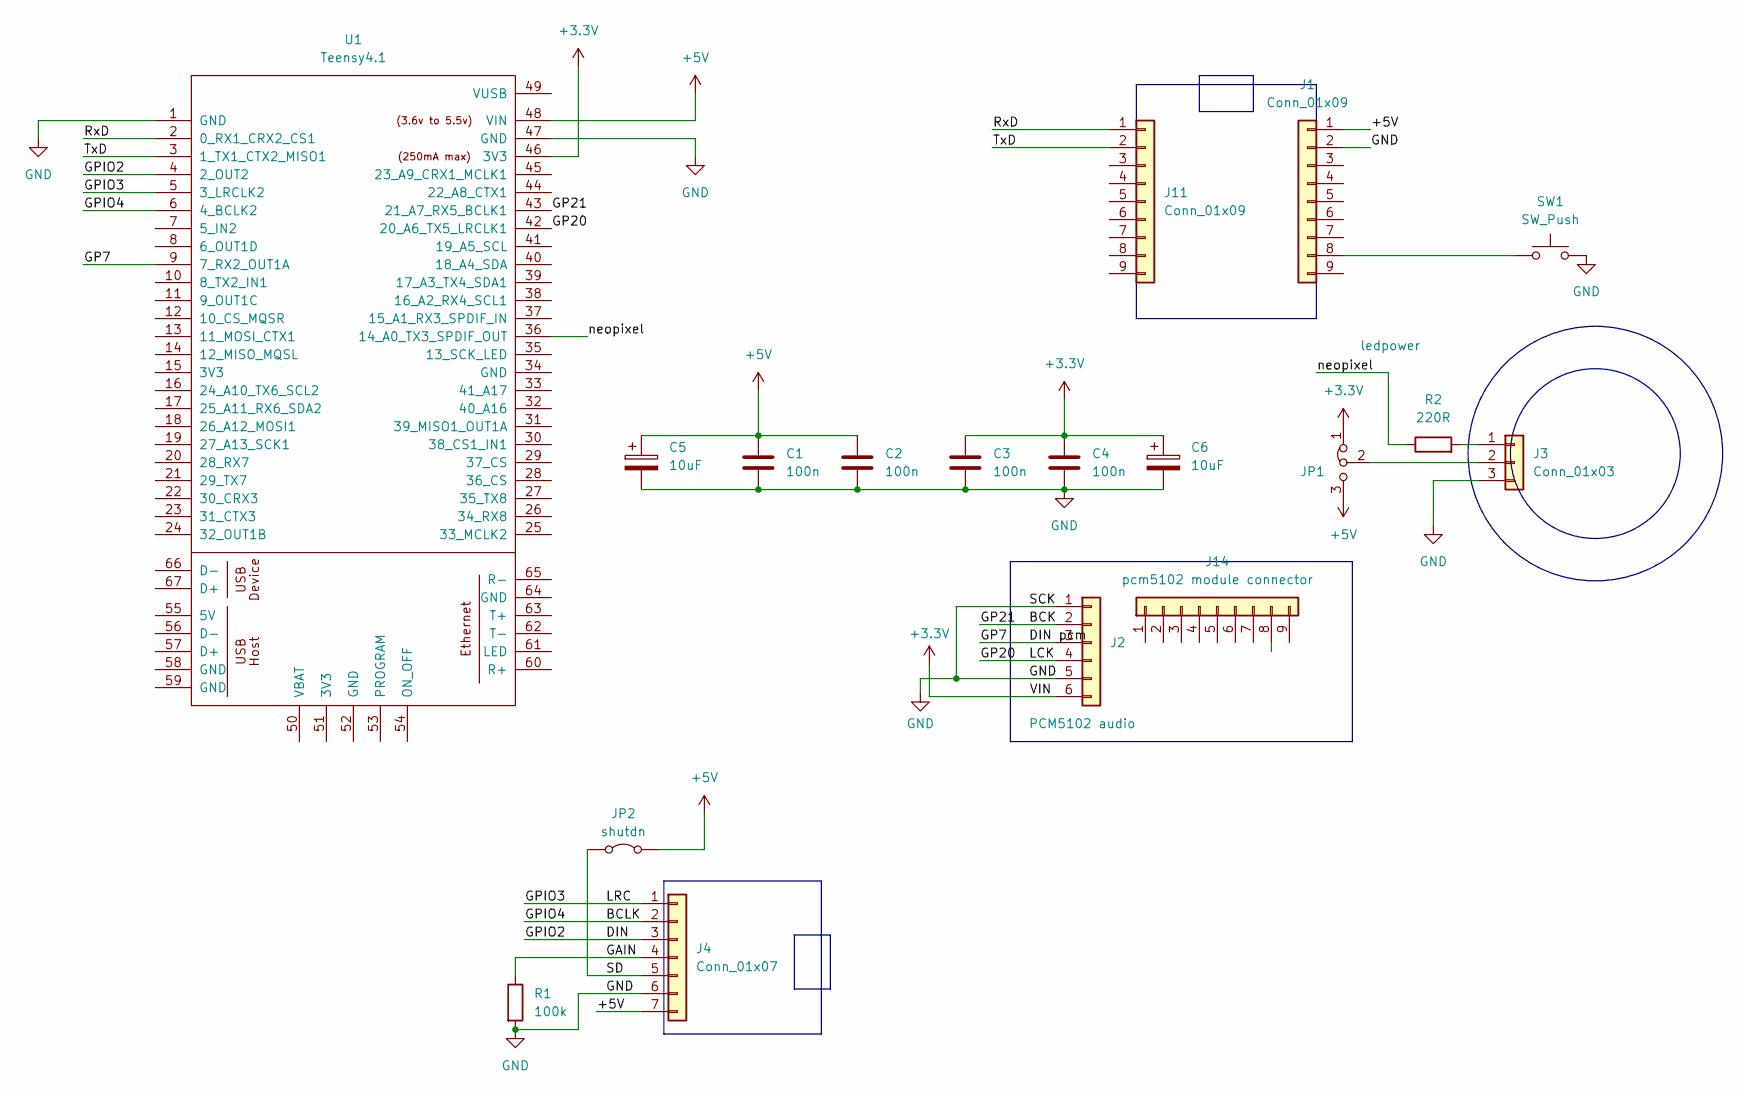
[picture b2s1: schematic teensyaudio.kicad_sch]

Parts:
C1, C2, C3, C4: 100n; C_0603_1608Metric_Pad1.08x0.95mm_HandSolder
C5, C6: 10uF; C_1206_3216Metric_Pad1.33x1.80mm_HandSolder
J1, J11: Conn_01x09; PinHeader_1x09_P2.54mm_Vertical
J2: PCM5102 audio; PinHeader_1x06_P2.54mm_Vertical
J3: Conn_01x03; PinHeader_1x03_P2.54mm_Vertical
J4: Conn_01x07; PinHeader_1x07_P2.54mm_Vertical
J14: pcm5102 module connector; PinHeader_1x09_P2.54mm_Vertical
JP1: ledpower; SolderJumper-3_P1.3mm_Bridged12_RoundedPad1.0x1.5mm
JP2: shutdn; SolderJumper-2_P1.3mm_Bridged_RoundedPad1.0x1.5mm
R1: 100k; R_0603_1608Metric_Pad0.98x0.95mm_HandSolder
R2: 220R; R_0603_1608Metric_Pad0.98x0.95mm_HandSolder
SW1: SW_Push; SW_PUSH_6mm
U1: Teensy4.1; Teensy41

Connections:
+3.3V: C3.1, C4.1, C6.1, J2.6, JP1.1 (A), U1.46 (3V3)
+5V: C1.1, C2.1, C5.1, J1.1, J4.7, JP1.3 (B), JP2.2 (B), U1.48 (VIN)
/BCK: J2.2, U1.43 (21_A7_RX5_BCLK1)
/BCLK: J4.2, U1.6 (4_BCLK2)
/DIN: J4.3, U1.4 (2_OUT2)
/DIN pcm: J2.3, U1.9 (7_RX2_OUT1A)
/GAIN: J4.4, R1.1
/GP20: J2.4, U1.42 (20_A6_TX5_LRCLK1)
/GPIO3: J4.1, U1.5 (3_LRCLK2)
/RxD: J11.1, U1.2 (0_RX1_CRX2_CS1)
/SD: J4.5, JP2.1 (A)
/TxD: J11.2, U1.3 (1_TX1_CTX2_MISO1)
/neopixel: R2.1, U1.36 (14_A0_TX3_SPDIF_OUT)
GND: C1.2, C2.2, C3.2, C4.2, C5.2, C6.2, J1.2, J2.1, J2.5, J3.3, J4.6, R1.2, SW1.2, U1.1 (GND), U1.47 (GND)
unnamed: J1.8, SW1.1
unnamed: J3.1, R2.2
unnamed: J3.2, JP1.2 (C)

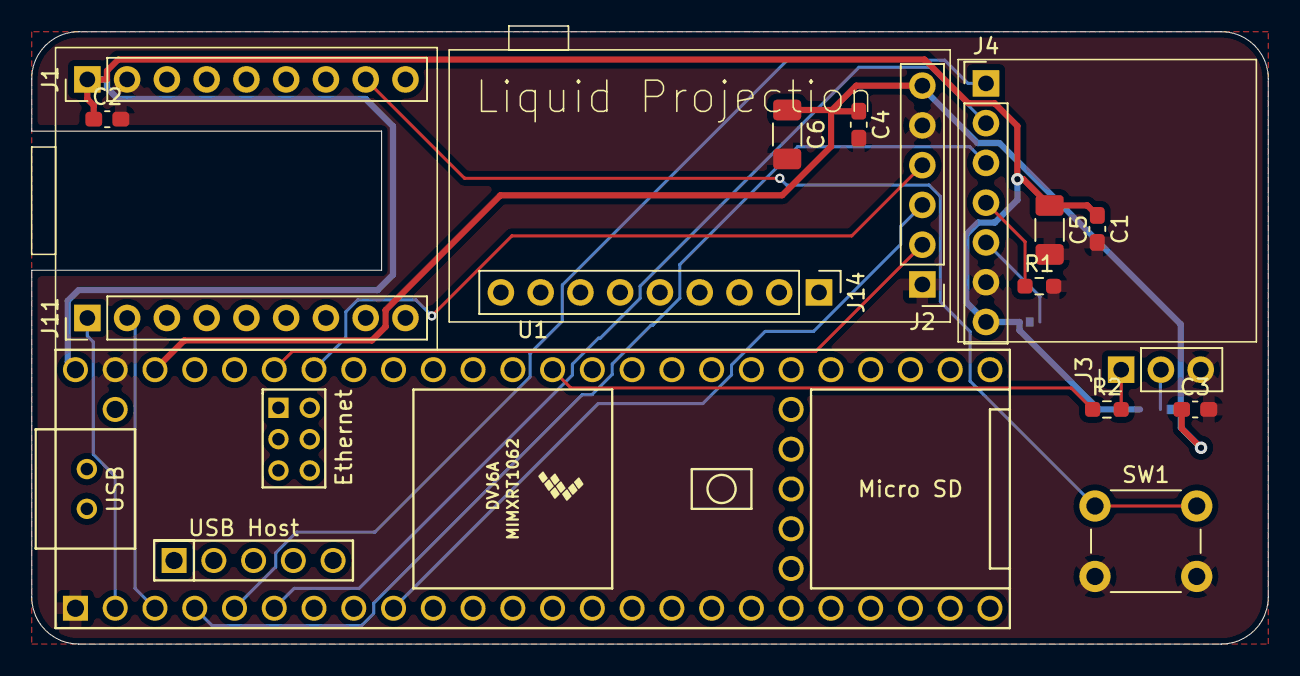
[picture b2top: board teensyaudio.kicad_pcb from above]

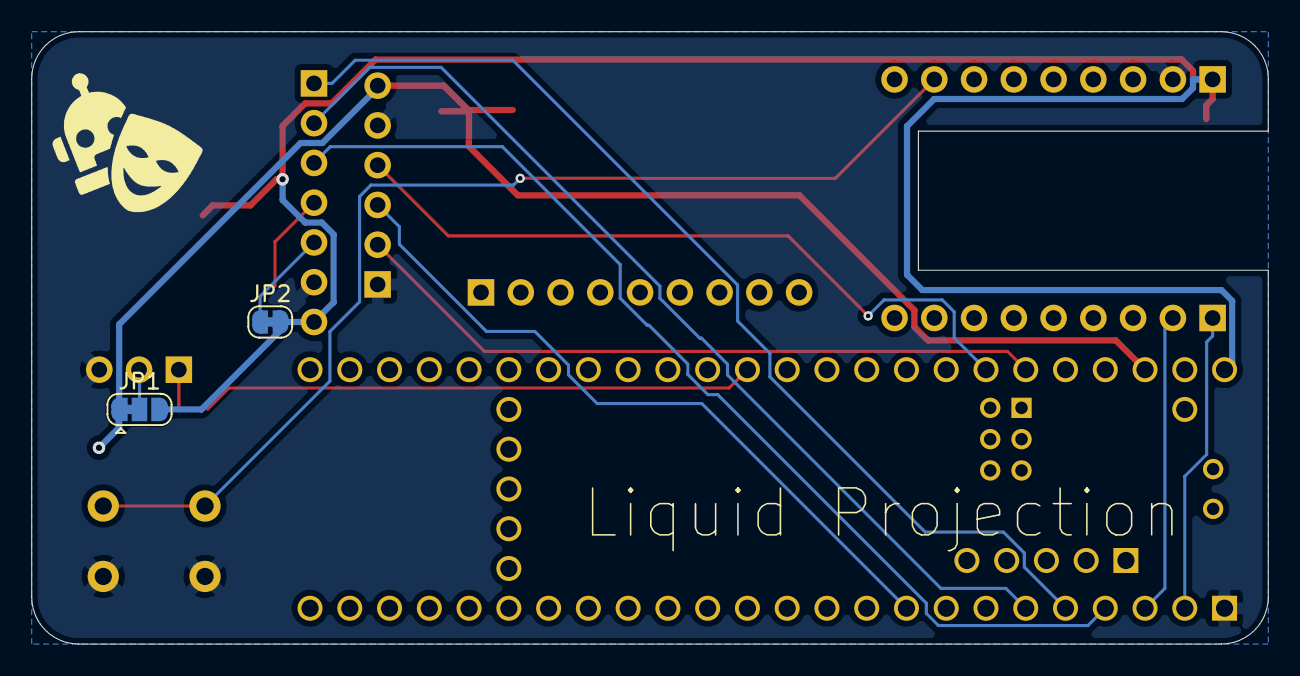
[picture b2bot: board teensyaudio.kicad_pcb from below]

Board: 2 copper layers, 79.0 x 39.1 mm, 19 parts (3 on the bottom side), 17 nets.

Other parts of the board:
G: LOGO; logo
